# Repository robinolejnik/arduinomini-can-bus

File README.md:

This board can be soldered with pinheaders onto an Arduino Mini. It contains the MCP2515 CAN bus controller and the MCP2551 CAN tranceiver.
The MCP2515 is connected to the hardware-SPI of the ATMega328p.

There are some jumpers:

| Jumper | Function                                                                                              |
| ------ |------------------------------------------------------------------------------------------------------ |
| TERM   | Connects an 120 Ohm bus termination to the CAN-lines.                                                 |
| SCK    | Connects the ATMega328p's clock output (Arduino pin 8/PB0/CLK0) to the MCP2515's clock input.         |
| CS     | Connects the MCP2515's chip select line to Arduino pin 10(PB2/SS).                                    |
| INT    | Connects the MCP2515's interrupt line to either Arduino pin 2 (PD2/INT0) or Arduino pin 3 (PD3/INT1). |

If you want to use other pins you can solder a wire to the jumper pad

View/Order the board on OSH Park: https://oshpark.com/shared_projects/cdqGDQ5q

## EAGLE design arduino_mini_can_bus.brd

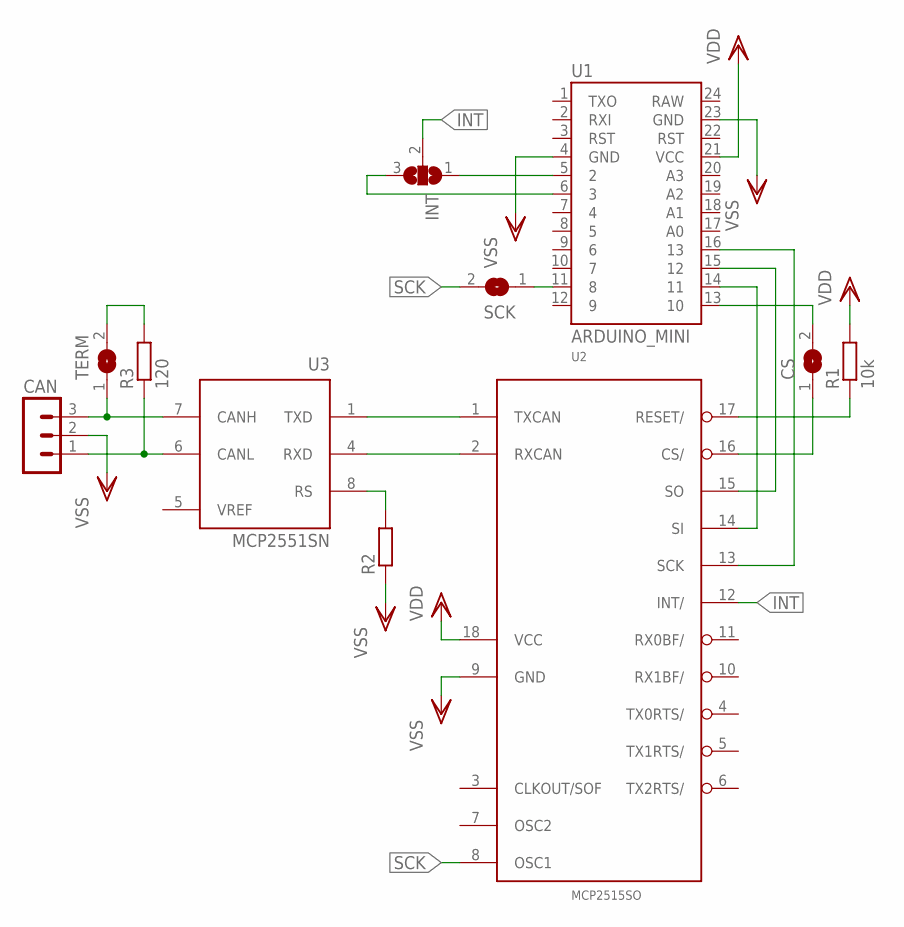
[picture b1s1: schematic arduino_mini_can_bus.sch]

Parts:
CAN: MA03-1
CS: SJ
INT: SJ2W; SJ_2
R1: 10k; 0207/10
R2: R-EU_0207/10; 0207/10
R3: 120; 0207/10
SCK: SJ
TERM: SJ
U1: ARDUINO_MINI
U2: MCP2515SO; SO18L
U3: MCP2551SN; SO-08

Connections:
INT: INT.2, U2.12 (INT/)
unnamed: U1.14 (11), U2.14 (SI)
unnamed: U1.15 (12), U2.15 (SO)
unnamed: U1.16 (13), U2.13 (SCK)
unnamed: CS.1, U2.16 (CS/)
unnamed: CS.2, U1.13 (10)
unnamed: U2.1 (TXCAN), U3.1 (TXD)
unnamed: U2.2 (RXCAN), U3.4 (RXD)
unnamed: CAN.1, R3.1, U3.6 (CANL)
unnamed: CAN.3, TERM.1, U3.7 (CANH)
unnamed: SCK.1, U1.11 (8)
unnamed: INT.1, U1.5 (2)
unnamed: R3.2, TERM.2
unnamed: R1.1, U2.17 (RESET/)
unnamed: R2.2, U3.8 (RS)
unnamed: INT.3, U1.6 (3)
SCK: SCK.2, U2.8 (OSC1)
VDD: R1.2, U1.21 (VCC), U2.18 (VCC), U3.3 (VDD)
VREF: U3.5 (VREF)
VSS: CAN.2, R2.1, U1.4 (GND), U1.23 (GND), U2.9 (GND), U3.2 (VSS)

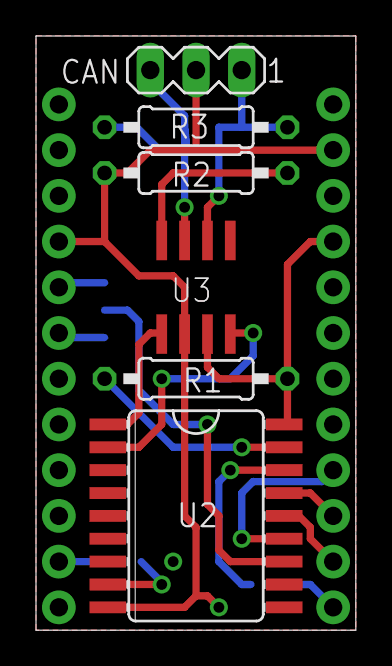
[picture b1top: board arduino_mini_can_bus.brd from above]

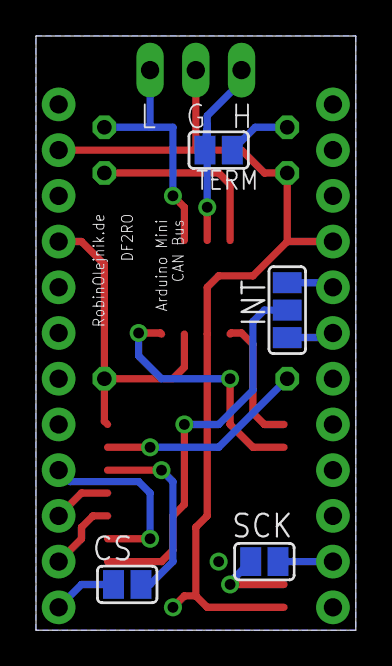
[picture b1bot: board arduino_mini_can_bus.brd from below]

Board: 2 copper layers, 17.8 x 33.0 mm, 11 parts (4 on the bottom side), 19 nets.

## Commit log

2016-04-17 Added eagle files and Readme
2021-10-12 Added converted KiCad-files and PDF schematic

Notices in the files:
parts and their libraries:
SparkFun-Boards: Licensing: Creative Commons ShareAlike 4.0 International - https://creativecommons.org/licenses/by-sa/4.0
